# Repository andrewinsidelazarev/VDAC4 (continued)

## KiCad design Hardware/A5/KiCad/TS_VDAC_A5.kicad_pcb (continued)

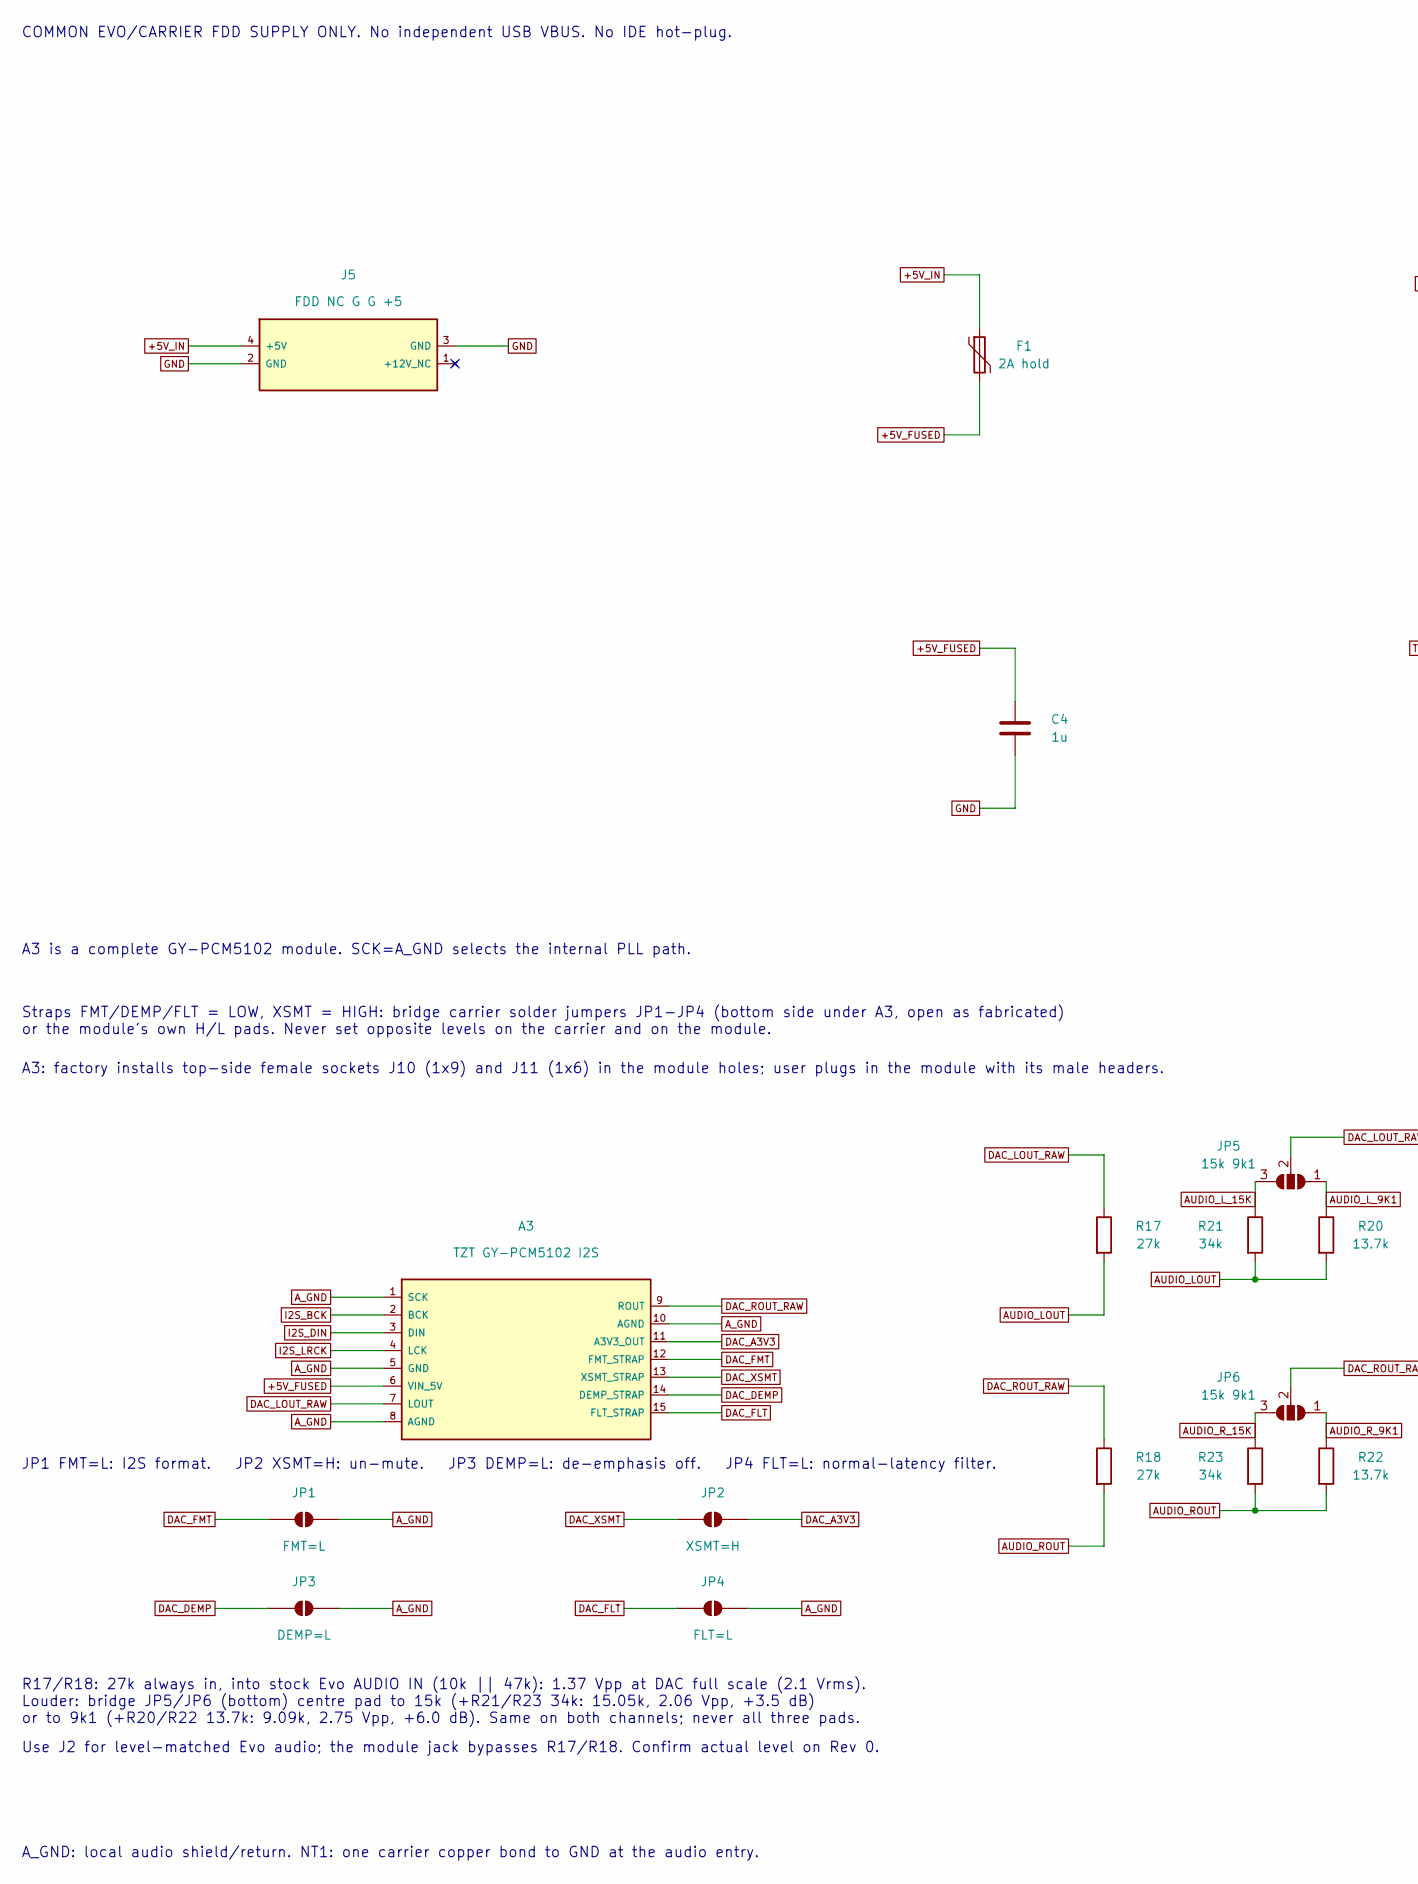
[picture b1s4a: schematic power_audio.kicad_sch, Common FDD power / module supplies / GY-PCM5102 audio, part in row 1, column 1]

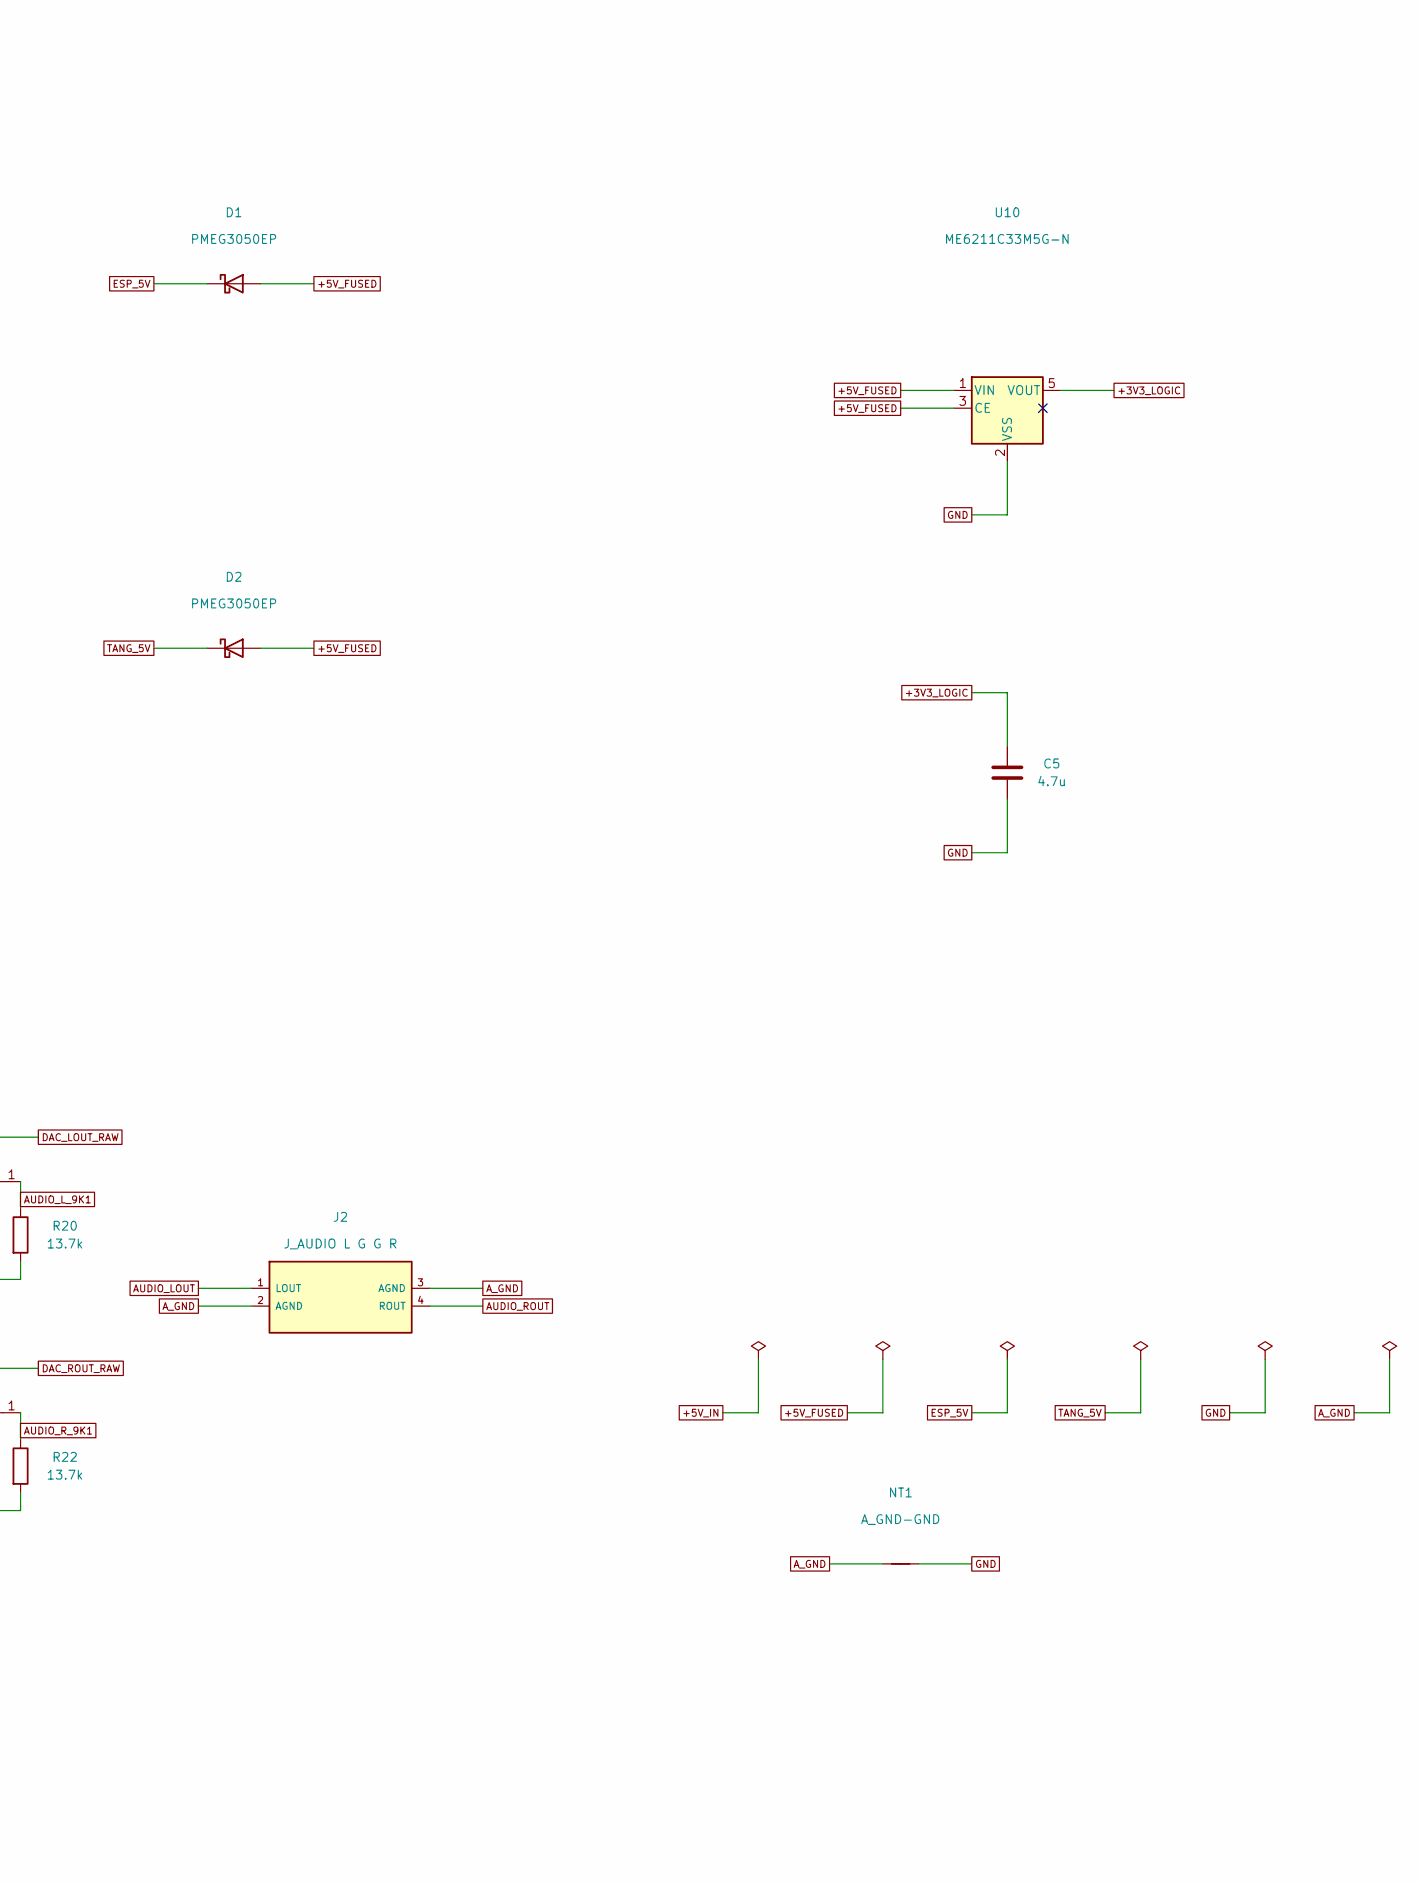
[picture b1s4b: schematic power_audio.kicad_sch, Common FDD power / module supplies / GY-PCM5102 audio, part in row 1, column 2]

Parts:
A3: TZT GY-PCM5102 I2S; GY_PCM5102_32x17_Provisional; MPN GY-PCM5102
C4: 1u; C_0805_2012Metric; MPN CL21B105KBFNNNE; LCSC C28323
C5: 4.7u; C_0805_2012Metric; MPN CL21A475KAQNNNE; LCSC C1779
D1, D2: PMEG3050EP; D_SOD-128; MPN PMEG3050EP,115; LCSC C50603
F1: 2A hold; Fuse_1812_4532Metric; MPN SMD1812P200TF16; LCSC C20812
J2: J_AUDIO L G G R; PinHeader_1x04_P2.54mm_Vertical; MPN PZ254V-11-04P; LCSC C2691448
J5: FDD NC G G +5; TE_171826-4_Horizontal_1x04_P2.50mm; MPN 171826-4; LCSC C590635
JP1: FMT=L; SolderJumper-2_P1.3mm_Open_RoundedPad1.0x1.5mm
JP2: XSMT=H; SolderJumper-2_P1.3mm_Open_RoundedPad1.0x1.5mm
JP3: DEMP=L; SolderJumper-2_P1.3mm_Open_RoundedPad1.0x1.5mm
JP4: FLT=L; SolderJumper-2_P1.3mm_Open_RoundedPad1.0x1.5mm
JP5, JP6: 15k 9k1; SolderJumper-3_P1.3mm_Open_RoundedPad1.0x1.5mm
NT1: A_GND-GND; NetTie-2_THT_Pad2.0mm_Drill1.0mm
R17, R18: 27k; R_0805_2012Metric; MPN 0805W8F2702T5E; LCSC C17593
R20, R22: 13.7k; R_0805_2012Metric; MPN 0805W8F1372T5E; LCSC C17448
R21, R23: 34k; R_0805_2012Metric; MPN 0805W8F3402T5E; LCSC C17640
U10: ME6211C33M5G-N; SOT-23-5; MPN ME6211C33M5G-N; LCSC C82942

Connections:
+3V3_LOGIC: C5.1, U10.5 (VOUT); also elsewhere on the board
+5V_FUSED: A3.6 (VIN_5V), C4.1, D1.2 (A), D2.2 (A), F1.2, U10.1 (VIN), U10.3 (CE); also elsewhere on the board
+5V_IN: F1.1, J5.4 (+5V)
AUDIO_LOUT: J2.1 (LOUT), R17.2, R20.2, R21.2
AUDIO_L_9K1: JP5.1 (A), R20.1
AUDIO_L_15K: JP5.3 (B), R21.1
AUDIO_ROUT: J2.4 (ROUT), R18.2, R22.2, R23.2
AUDIO_R_9K1: JP6.1 (A), R22.1
AUDIO_R_15K: JP6.3 (B), R23.1
A_GND: A3.1 (SCK), A3.5 (GND), A3.8 (AGND), A3.10 (AGND), J2.2 (AGND), J2.3 (AGND), JP1.2 (B), JP3.2 (B), JP4.2 (B), NT1.1
DAC_A3V3: A3.11 (A3V3_OUT), JP2.2 (B)
DAC_DEMP: A3.14 (DEMP_STRAP), JP3.1 (A)
DAC_FLT: A3.15 (FLT_STRAP), JP4.1 (A)
DAC_FMT: A3.12 (FMT_STRAP), JP1.1 (A)
DAC_LOUT_RAW: A3.7 (LOUT), JP5.2 (C), R17.1
DAC_ROUT_RAW: A3.9 (ROUT), JP6.2 (C), R18.1
DAC_XSMT: A3.13 (XSMT_STRAP), JP2.1 (A)
ESP_5V: D1.1 (K); also elsewhere on the board
GND: C4.2, C5.2, J5.2 (GND), J5.3 (GND), NT1.2, U10.2 (VSS); also elsewhere on the board
I2S_BCK: A3.2 (BCK); also elsewhere on the board
I2S_DIN: A3.3 (DIN); also elsewhere on the board
I2S_LRCK: A3.4 (LCK); also elsewhere on the board
TANG_5V: D2.1 (K); also elsewhere on the board

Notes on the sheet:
COMMON EVO/CARRIER FDD SUPPLY ONLY. No independent USB VBUS. No IDE hot-plug.
A3 is a complete GY-PCM5102 module. SCK=A_GND selects the internal PLL path.
Straps FMT/DEMP/FLT = LOW, XSMT = HIGH: bridge carrier solder jumpers JP1-JP4 (bottom side under A3, open as fabricated) or the module's own H/L pads. Never set opposite levels on the carrier and on the module.
A3: factory installs top-side female sockets J10 (1x9) and J11 (1x6) in the module holes; user plugs in the module with its male headers.
JP1 FMT=L: I2S format. JP2 XSMT=H: un-mute. JP3 DEMP=L: de-emphasis off. JP4 FLT=L: normal-latency filter.
R17/R18: 27k always in, into stock Evo AUDIO IN (10k || 47k): 1.37 Vpp at DAC full scale (2.1 Vrms). Louder: bridge JP5/JP6 (bottom) centre pad to 15k (+R21/R23 34k: 15.05k, 2.06 Vpp, +3.5 dB) or to 9k1 (+R20/R22 13.7k: 9.09k, 2.75 Vpp, +6.0 dB). Same on both channels; never all three pads.
Use J2 for level-matched Evo audio; the module jack bypasses R17/R18. Confirm actual level on Rev 0.
A_GND: local audio shield/return. NT1: one carrier copper bond to GND at the audio entry.

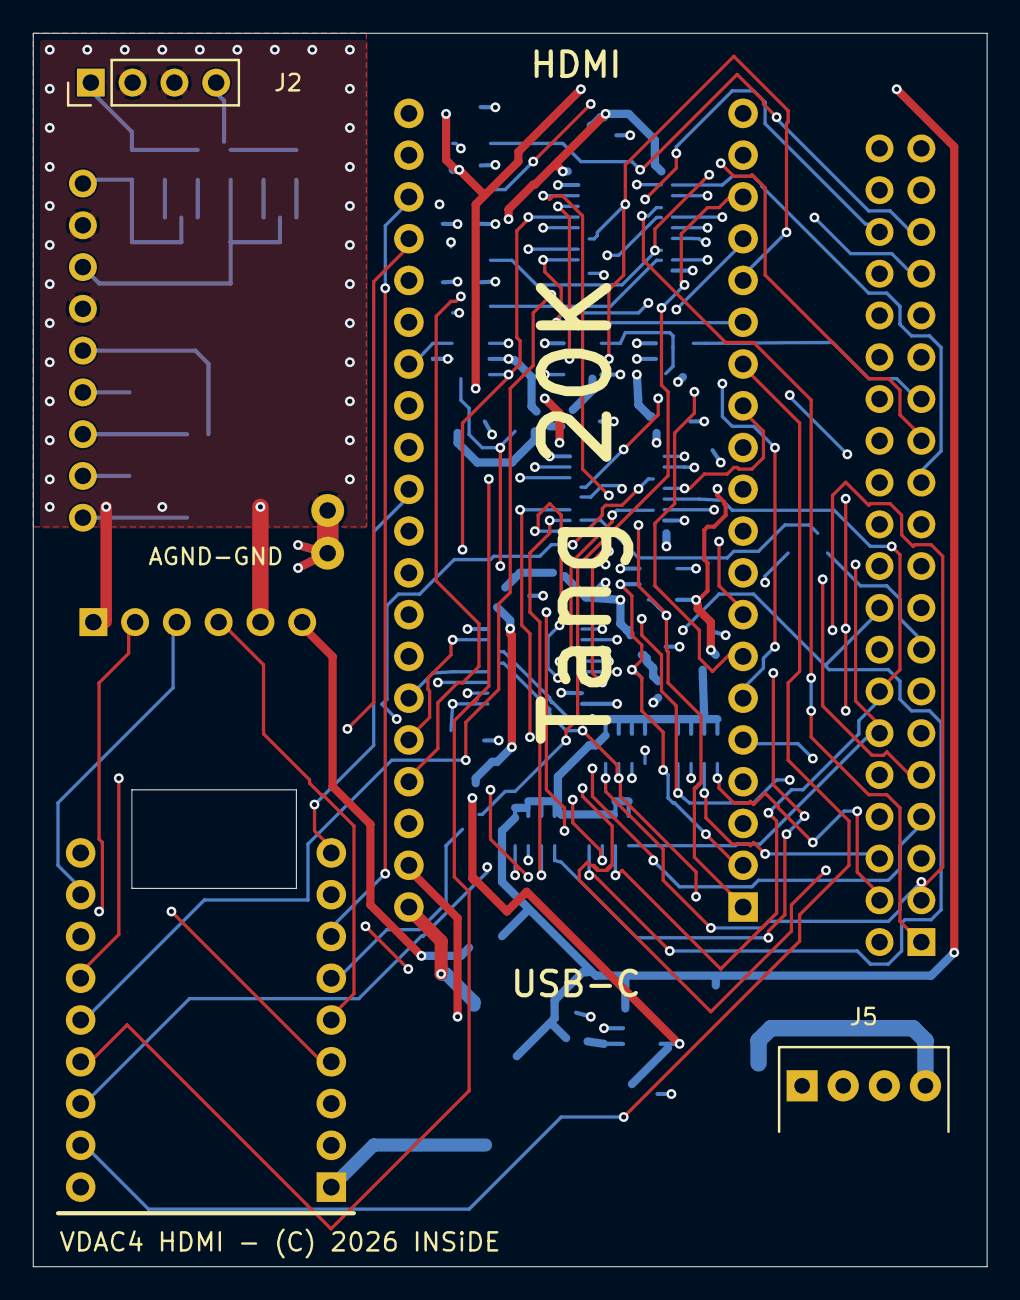
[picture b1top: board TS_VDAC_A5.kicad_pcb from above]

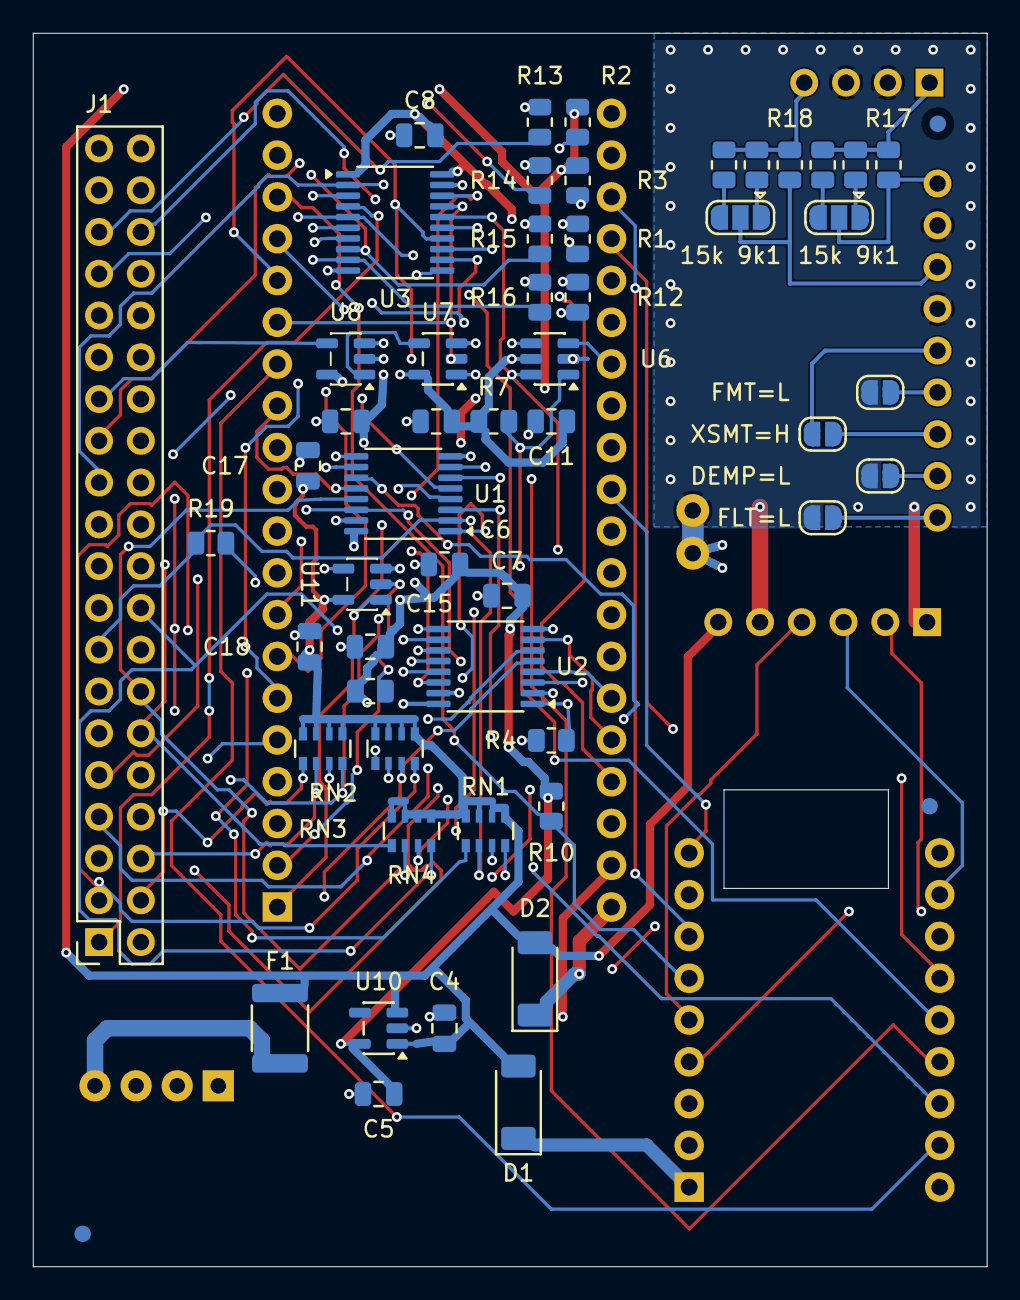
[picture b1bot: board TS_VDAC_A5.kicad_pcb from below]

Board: 4 copper layers, 58.0 x 75.0 mm, 61 parts (55 on the bottom side), 78 nets.

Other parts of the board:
FID1, FID2, FID3: Fiducial_1mm_Mask2mm

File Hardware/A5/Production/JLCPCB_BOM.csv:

Comment,Designator,Footprint,LCSC Part #,MPN,Manufacturer,Quantity,Side,Mount,Notes
1u,C4,C_0805_2012Metric,C28323,CL21B105KBFNNNE,Samsung Electro-Mechanics,1,Bottom,SMT,Carrier SMD on BOTTOM
4.7u,C5,C_0805_2012Metric,C1779,CL21A475KAQNNNE,Samsung Electro-Mechanics,1,Bottom,SMT,Carrier SMD on BOTTOM
100n,"C6,C7,C8,C11,C12,C13,C15,C17,C18",C_0805_2012Metric,C49678,CC0805KRX7R9BB104,YAGEO,9,Bottom,SMT,Carrier SMD on BOTTOM
PMEG3050EP,"D1,D2",D_SOD-128,C50603,"PMEG3050EP,115",Nexperia,2,Bottom,SMT,Carrier SMD on BOTTOM
2A hold,F1,Fuse_1812_4532Metric,C20812,SMD1812P200TF16,RUILON(Shenzhen Ruilongyuan Elec),1,Bottom,SMT,Carrier SMD on BOTTOM
TS-PORT40,J1,PinSocket_2x20_P2.54mm_Vertical,C2977589,2.54-2*20,ZHOURI,1,Bottom,THT,"Female IDE socket body BELOW carrier, solder from ABOVE; direct mating to Evo X2"
J_AUDIO L G G R,J2,PinHeader_1x04_P2.54mm_Vertical,C2691448,PZ254V-11-04P,XFCN,1,Top,THT,Factory installs carrier connector on TOP
FDD NC G G +5,J5,TE_171826-4_Horizontal_1x04_P2.50mm,C590635,171826-4,TE Connectivity,1,Top,THT,Factory installs carrier connector on TOP; cable +Y/down; nominal front overhang 0.3mm; finished holes 0.95 +/-0.05mm
Female socket 1x20 P2.54mm,"J6,J7",PinSocket_1x20_P2.54mm_Vertical,C5224030,PM2.54-1*20,ZHOURI,2,Top,THT,"TOP, mates with Tang J5; shares parent footprint pads; ZHOURI, body height 8.5mm | TOP, mates with Tang J6; shares parent footprint pads; ZHOURI, body height 8.5mm"
Female socket 1x9 P2.54mm,"J8,J9,J10",PinSocket_1x09_P2.54mm_Vertical,C5224028,PM2.54-1*9,ZHOURI,3,Top,THT,"TOP, mates with ESP 5V/GPIO1-6 row; shares parent footprint pads; ZHOURI, body height 8.5mm | TOP, mates with ESP GPIO43/44/GPIO13-7 row; shares parent footprint pads; ZHOURI, body height 8.5mm | TOP, mates with GY-PCM5102 LOUT..FLT row (A3.7-A3.15); shares parent footprint pads; ZHOURI, body height 8.5mm"
Female socket 1x6 P2.54mm,J11,PinSocket_1x06_P2.54mm_Vertical,C5224026,PM2.54-1*6,ZHOURI,1,Top,THT,"TOP, mates with GY-PCM5102 SCK..VIN row (A3.1-A3.6); shares parent footprint pads; ZHOURI, body height 8.5mm"
47k,"R1,R7,R9,R12,R13,R14,R15,R16",R_0805_2012Metric,C17713,0805W8F4702T5E,UNI-ROYAL(Uniroyal Elec),8,Bottom,SMT,Carrier SMD on BOTTOM
10k,"R2,R3,R10",R_0805_2012Metric,C17414,0805W8F1002T5E,UNI-ROYAL(Uniroyal Elec),3,Bottom,SMT,Carrier SMD on BOTTOM
1k,"R4,R19",R_0805_2012Metric,C17513,0805W8F1001T5E,UNI-ROYAL(Uniroyal Elec),2,Bottom,SMT,Carrier SMD on BOTTOM
27k,"R17,R18",R_0805_2012Metric,C17593,0805W8F2702T5E,UNI-ROYAL(Uniroyal Elec),2,Bottom,SMT,Carrier SMD on BOTTOM
13.7k,"R20,R22",R_0805_2012Metric,C17448,0805W8F1372T5E,UNI-ROYAL(Uniroyal Elec),2,Bottom,SMT,Carrier SMD on BOTTOM
34k,"R21,R23",R_0805_2012Metric,C17640,0805W8F3402T5E,UNI-ROYAL(Uniroyal Elec),2,Bottom,SMT,Carrier SMD on BOTTOM
4x47k,"RN1,RN2,RN3,RN4",R_Array_Convex_4x0603,C779384,YC164-JR-0747KL,YAGEO,4,Bottom,SMT,Carrier SMD on BOTTOM
SN74LVC257APWR,"U1,U2",TSSOP-16_4.4x5mm_P0.65mm,C205921,SN74LVC257APWR,Texas Instruments,2,Bottom,SMT,Carrier SMD on BOTTOM
SN74LVC245APW,U3,TSSOP-20_4.4x6.5mm_P0.65mm,C7848,SN74LVC245APWR,Texas Instruments,1,Bottom,SMT,Carrier SMD on BOTTOM
SN74LVC1G97,U6,SOT-23-6,C128411,SN74LVC1G97DBVR,Texas Instruments,1,Bottom,SMT,Carrier SMD on BOTTOM
SN74LVC1G00DBVR,U7,SOT-23-5,C7826,SN74LVC1G00DBVR,Texas Instruments,1,Bottom,SMT,Carrier SMD on BOTTOM
74AHCT1G126GV,"U8,U11",SOT-23-5,C52140416,74AHCT1G126GV,MDD(Microdiode Semiconductor),2,Bottom,SMT,Carrier SMD on BOTTOM
ME6211C33M5G-N,U10,SOT-23-5,C82942,ME6211C33M5G-N,MICRONE(Nanjing Micro One Elec),1,Bottom,SMT,Carrier SMD on BOTTOM

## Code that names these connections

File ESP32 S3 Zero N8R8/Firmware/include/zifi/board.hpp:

#pragma once

#include <stdint.h>

// Привязка прошивки к плате. Сборку выбирает определение ZIFI_BOARD_VDAC4:
//   1         — несущая плата VDAC4 A3.1 (обмен по SPI платы ZX Evolution, ЦАП PCM5102);
//   не задано — стенды ПК (tools/host_*, tests): исходники прошивки без канала SPI,
//               звука и прочего оборудования платы. Сама прошивка так не собирается.
//
// Номера выводов VDAC4 взяты из Tang Nano 20k/Docs/a3-interface-pinmap.md.

// Каталог публикации образа VDAC4 на raw.githubusercontent.com: репозиторий VDAC4,
// ветка main, папка Firmware/firmware/vdac4 (firmware.sha256 и firmware.bin; пробелы
// в пути — %20, строка запроса уходит как есть). Обновление из сети берёт образ
// только для своей платы. Вне блока платы — чтобы тот же адрес брала программа
// ESP для Unreal (tools/unreal), которая собирается без ZIFI_BOARD_VDAC4.
#define ZIFI_UPDATE_DIRECTORY \
  "/andrewinsidelazarev/VDAC4/refs/heads/main/ESP32%20S3%20Zero%20N8R8/Firmware/firmware/vdac4/"

#if defined(ZIFI_BOARD_VDAC4) && ZIFI_BOARD_VDAC4

#define ZIFI_HAS_SPI_LINK 1
#define ZIFI_HAS_AUDIO 1
#define ZIFI_HAS_STATUS_LED 1
// Флешка в разъёме USB-C модуля (USB OTG хостом): кэш ресурсов музыки.
#define ZIFI_HAS_USB_DRIVE 1

namespace zifi {
namespace board {

constexpr char kName[] = "VDAC4-A3.1";
// Формат номера версии этой платы: по нему сравниваются установленная и опубликованная.
constexpr char kReleaseVersionFormat[] = "vdac4-%u.%u.%u%n";

// SPI Evo -> ESP. ESP здесь всегда ведомый: обратный драйвер платы однонаправленный,
// и режим ведущего ESP на этой плате запрещён. Выводы совпадают с IO_MUX порта SPI2.
constexpr int kSpiCsPin = 10;
constexpr int kSpiMosiPin = 11;
constexpr int kSpiSckPin = 12;
constexpr int kSpiMisoPin = 13;
// Когда ESP выставляет на MISO очередной бит. В режиме 0 ведомому положено
// делать это по спаду SCK, а Evo читает бит по следующему фронту, через
// полтакта (36 нс при 14 МГц). На этой плате такт идёт к ESP через буфер Evo и
// U3, а данные обратно — через U6 и U8, и вместе с самим ESP это те же
// полтакта: бит приходит к Evo в момент выборки, и она читает то его, то
// предыдущий (esp_info видел 2D EF 00 и 3D FB 01 вместо 5A D7 01). Поэтому бит
// выставляется на полтакта раньше, по фронту SCK: к выборке он стоит уже
// полтакта, а сменится ещё через столько же.
constexpr bool kSpiMisoEarly = true;

// I2S -> GY-PCM5102 (SCK модуля на земле: ЦАП берёт тактовую из BCK).
constexpr int kI2sBckPin = 1;
constexpr int kI2sLrckPin = 2;
constexpr int kI2sDataPin = 8;

// Светодиод WS2812 самого модуля ESP32-S3-Zero; на плату этот вывод не выходит.
constexpr int kStatusLedPin = 21;

// Линии LINK к Tang Nano 20K (QSPI и запрос прерывания). Обмена по ним пока нет:
// они остаются входами и не мешают FPGA.
//   GPIO3 CS, GPIO5 SCK, GPIO4 IO0, GPIO7 IO1, GPIO6 IO2, GPIO44 IO3, GPIO9 IRQ.
// GPIO44 — это ещё и RX UART0, поэтому UART0 на этой плате не используется вовсе.
//
// LINK CS на плате подтянут резистором R10 (10 кОм) к +3,3 В её логики. По нему
// прошивка узнаёт, стоит ли модуль в плате и есть ли на плате питание.
constexpr int kLinkCsPin = 3;

}  // namespace board
}  // namespace zifi

#else

#define ZIFI_HAS_SPI_LINK 0
#define ZIFI_HAS_AUDIO 0
#define ZIFI_HAS_STATUS_LED 0
#define ZIFI_HAS_USB_DRIVE 0

#endif

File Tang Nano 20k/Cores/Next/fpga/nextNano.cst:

// clk
IO_LOC "clk_27m" 4;
IO_PORT "clk_27m" IO_TYPE=LVCMOS33 PULL_MODE=NONE;

// leds
IO_LOC "led[5]" 20;
IO_PORT "led[5]" IO_TYPE=LVCMOS33 PULL_MODE=NONE DRIVE=8;
IO_LOC "led[4]" 19;
IO_PORT "led[4]" IO_TYPE=LVCMOS33 PULL_MODE=NONE DRIVE=8;
IO_LOC "led[3]" 18;
IO_PORT "led[3]" IO_TYPE=LVCMOS33 PULL_MODE=NONE DRIVE=8;
IO_LOC "led[2]" 17;
IO_PORT "led[2]" IO_TYPE=LVCMOS33 PULL_MODE=NONE DRIVE=8;
IO_LOC "led[1]" 16;
IO_PORT "led[1]" IO_TYPE=LVCMOS33 PULL_MODE=NONE DRIVE=8;
IO_LOC "led[0]" 15;
IO_PORT "led[0]" IO_TYPE=LVCMOS33 PULL_MODE=NONE DRIVE=8;

// hw buttons
IO_LOC "btn[0]" 88; // S1
IO_PORT "btn[0]" PULL_MODE=NONE IO_TYPE=LVCMOS33;
IO_LOC "btn[1]" 87; // S2
IO_PORT "btn[1]" PULL_MODE=NONE IO_TYPE=LVCMOS33;

// SD card
// IO_LOC "SD_MOSI" 82;
// IO_PORT "SD_MOSI" IO_TYPE=LVCMOS33 PULL_MODE=NONE;
// IO_LOC "SD_SCK" 83;
// IO_PORT "SD_SCK" IO_TYPE=LVCMOS33 PULL_MODE=NONE;
// IO_LOC "SD_CS" 81;
// IO_PORT "SD_CS" IO_TYPE=LVCMOS33 PULL_MODE=NONE;
// IO_LOC "SD_MISO" 84;
// IO_PORT "SD_MISO" IO_TYPE=LVCMOS33 PULL_MODE=NONE;

// SD card - SPI mode
IO_LOC "SD_SCK" 83;
IO_PORT "SD_SCK" IO_TYPE=LVCMOS33 PULL_MODE=NONE;

IO_LOC "SD_MOSI" 82;
IO_PORT "SD_MOSI" IO_TYPE=LVCMOS33 PULL_MODE=NONE;

IO_LOC "SD_CS" 81;
IO_PORT "SD_CS" IO_TYPE=LVCMOS33 PULL_MODE=NONE;

IO_LOC "SD_MISO" 84;
IO_PORT "SD_MISO" IO_TYPE=LVCMOS33 PULL_MODE=NONE;

// Unused SDIO lines - keep high in SPI mode
 IO_LOC "SD_D1" 85;
 IO_PORT "SD_D1" IO_TYPE=LVCMOS33 PULL_MODE=NONE;
 IO_LOC "SD_D2" 80;
 IO_PORT "SD_D2" IO_TYPE=LVCMOS33 PULL_MODE=NONE;

// UART USB-C
// IO_LOC "UART_RX" 70;
// IO_LOC "UART_TX" 69;
// IO_PORT "UART_RX" IO_TYPE=LVCMOS33;
// IO_PORT "UART_TX" IO_TYPE=LVCMOS33;

//LCD
// IO_LOC "lcd_dclk" 77;
// IO_LOC "lcd_hs" 25;
// IO_LOC "lcd_vs" 26;
// IO_LOC "lcd_de" 48;
// IO_LOC "lcd_r[0]" 42;
// IO_LOC "lcd_r[1]" 41;
// IO_LOC "lcd_r[2]" 40;
// IO_LOC "lcd_r[3]" 39;
// IO_LOC "lcd_r[4]" 38;
// IO_LOC "lcd_g[0]" 37;
// IO_LOC "lcd_g[1]" 36;
// IO_LOC "lcd_g[2]" 35;
// IO_LOC "lcd_g[3]" 34;
// IO_LOC "lcd_g[4]" 33;
// IO_LOC "lcd_g[5]" 32;
// IO_LOC "lcd_b[0]" 31;
// IO_LOC "lcd_b[1]" 30;
// IO_LOC "lcd_b[2]" 29;
// IO_LOC "lcd_b[3]" 28;
// IO_LOC "lcd_b[4]" 27;
// IO_PORT "lcd_dclk" IO_TYPE=LVCMOS33;
// IO_PORT "lcd_hs"   IO_TYPE=LVCMOS33;
// IO_PORT "lcd_vs"   IO_TYPE=LVCMOS33;
// IO_PORT "lcd_de"   IO_TYPE=LVCMOS33;
// IO_PORT "lcd_r[0]" IO_TYPE=LVCMOS33 DRIVE=24;
// IO_PORT "lcd_r[1]" IO_TYPE=LVCMOS33 DRIVE=24;
// IO_PORT "lcd_r[2]" IO_TYPE=LVCMOS33 DRIVE=24;
// IO_PORT "lcd_r[3]" IO_TYPE=LVCMOS33 DRIVE=24;
// IO_PORT "lcd_r[4]" IO_TYPE=LVCMOS33 DRIVE=24;
// IO_PORT "lcd_g[0]" IO_TYPE=LVCMOS33 DRIVE=24;
// IO_PORT "lcd_g[1]" IO_TYPE=LVCMOS33 DRIVE=24;
// IO_PORT "lcd_g[2]" IO_TYPE=LVCMOS33 DRIVE=24;
// IO_PORT "lcd_g[3]" IO_TYPE=LVCMOS33 DRIVE=24;
// IO_PORT "lcd_g[4]" IO_TYPE=LVCMOS33 DRIVE=24;
// IO_PORT "lcd_g[5]" IO_TYPE=LVCMOS33 DRIVE=24;
// IO_PORT "lcd_b[0]" IO_TYPE=LVCMOS33 DRIVE=24;
// IO_PORT "lcd_b[1]" IO_TYPE=LVCMOS33 DRIVE=24;
// IO_PORT "lcd_b[2]" IO_TYPE=LVCMOS33 DRIVE=24;
// IO_PORT "lcd_b[3]" IO_TYPE=LVCMOS33 DRIVE=24;
// IO_PORT "lcd_b[4]" IO_TYPE=LVCMOS33 DRIVE=24;


IO_LOC "O_tmds_clk_p" 33,34;
IO_PORT "O_tmds_clk_p" PULL_MODE=NONE DRIVE=8;
IO_LOC "O_tmds_data_p[0]" 35,36;
IO_PORT "O_tmds_data_p[0]" PULL_MODE=NONE DRIVE=8;
IO_LOC "O_tmds_data_p[1]" 37,38;
IO_PORT "O_tmds_data_p[1]" PULL_MODE=NONE DRIVE=8;
IO_LOC "O_tmds_data_p[2]" 39,40;
IO_PORT "O_tmds_data_p[2]" PULL_MODE=NONE DRIVE=8;

// audio amplifier
IO_LOC "i2s_en" 51;
IO_PORT "i2s_en" PULL_MODE=UP DRIVE=8 IO_TYPE=LVCMOS33;
IO_LOC "i2s_sdata" 54;
IO_PORT "i2s_sdata" PULL_MODE=UP DRIVE=8 IO_TYPE=LVCMOS33;
IO_LOC "i2s_lrck" 55;
IO_PORT "i2s_lrck" PULL_MODE=UP DRIVE=8 IO_TYPE=LVCMOS33;
IO_LOC "i2s_bclk" 56;
IO_PORT "i2s_bclk" PULL_MODE=UP DRIVE=8 IO_TYPE=LVCMOS33;

// connection to the external BL616/M0S
IO_LOC "m0s[0]" 52; // was 42 - spi_dir = spi_io_dout - SPI data from FPGA to MCU - GPIO10
IO_PORT "m0s[0]" PULL_MODE=UP IO_TYPE=LVCMOS33;
IO_LOC "m0s[1]" 53;  // was 41 - SPI data from MCU to FPGA - GPIO11
IO_PORT "m0s[1]" PULL_MODE=UP IO_TYPE=LVCMOS33;
IO_LOC "m0s[2]" 71; // was 56 - SPI select, active low - GPIO12
IO_PORT "m0s[2]" PULL_MODE=UP IO_TYPE=LVCMOS33;
IO_LOC "m0s[3]" 72; // was 54 - SPI clock, idle low - GPIO13
IO_PORT "m0s[3]" PULL_MODE=UP IO_TYPE=LVCMOS33;
IO_LOC "m0s[4]" 48; // was 51 - IRQ - Interrupt from FPGA to MCU, active low - GPIO14
IO_PORT "m0s[4]" PULL_MODE=UP IO_TYPE=LVCMOS33;
//IO_LOC "m0s[5]" 48;
//IO_PORT "m0s[5]" PULL_MODE=UP IO_TYPE=LVCMOS33;

// connections to the internal BL616 controller
IO_LOC "spi_csn" 86;
IO_PORT "spi_csn" PULL_MODE=UP IO_TYPE=LVCMOS33;
IO_LOC "spi_sclk" 13;
IO_PORT "spi_sclk" PULL_MODE=UP IO_TYPE=LVCMOS33;
IO_LOC "spi_dat" 76;
IO_PORT "spi_dat" PULL_MODE=UP IO_TYPE=LVCMOS33;
IO_LOC "spi_dir" 75;
IO_PORT "spi_dir" PULL_MODE=NONE DRIVE=8 IO_TYPE=LVCMOS33;
IO_LOC "spi_irqn" 69; // USB-C UART TX output
IO_PORT "spi_irqn" PULL_MODE=NONE DRIVE=8 IO_TYPE=LVCMOS33;
